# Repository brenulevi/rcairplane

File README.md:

# RC Airplane

### Used components:
Airplane:
- 1x ESP32 DevKit 1
- 1x nRF24L01+ PA/LNA Ext. Antenna
- 1x ESC 30A
- 1x Brushless DC Motor 2200kv
- 4x 9g Servo Motor
- 4x LED (1R, 1G, 2W)
- 4x Resistor 330
- 1x Polarized Capacitor 10uF
- 1x AMS1117-3.3V
- 1x UBEC 5V/3A Freewing
- 1x MPU6050
- 1x BMP280
- 1x ADS1115
- 1x 5200mAh 3S Lipo Battery

Control:
- 1x Arduino Nano
- 1x nRF24L01+ PA/LNA Ext. Antenna

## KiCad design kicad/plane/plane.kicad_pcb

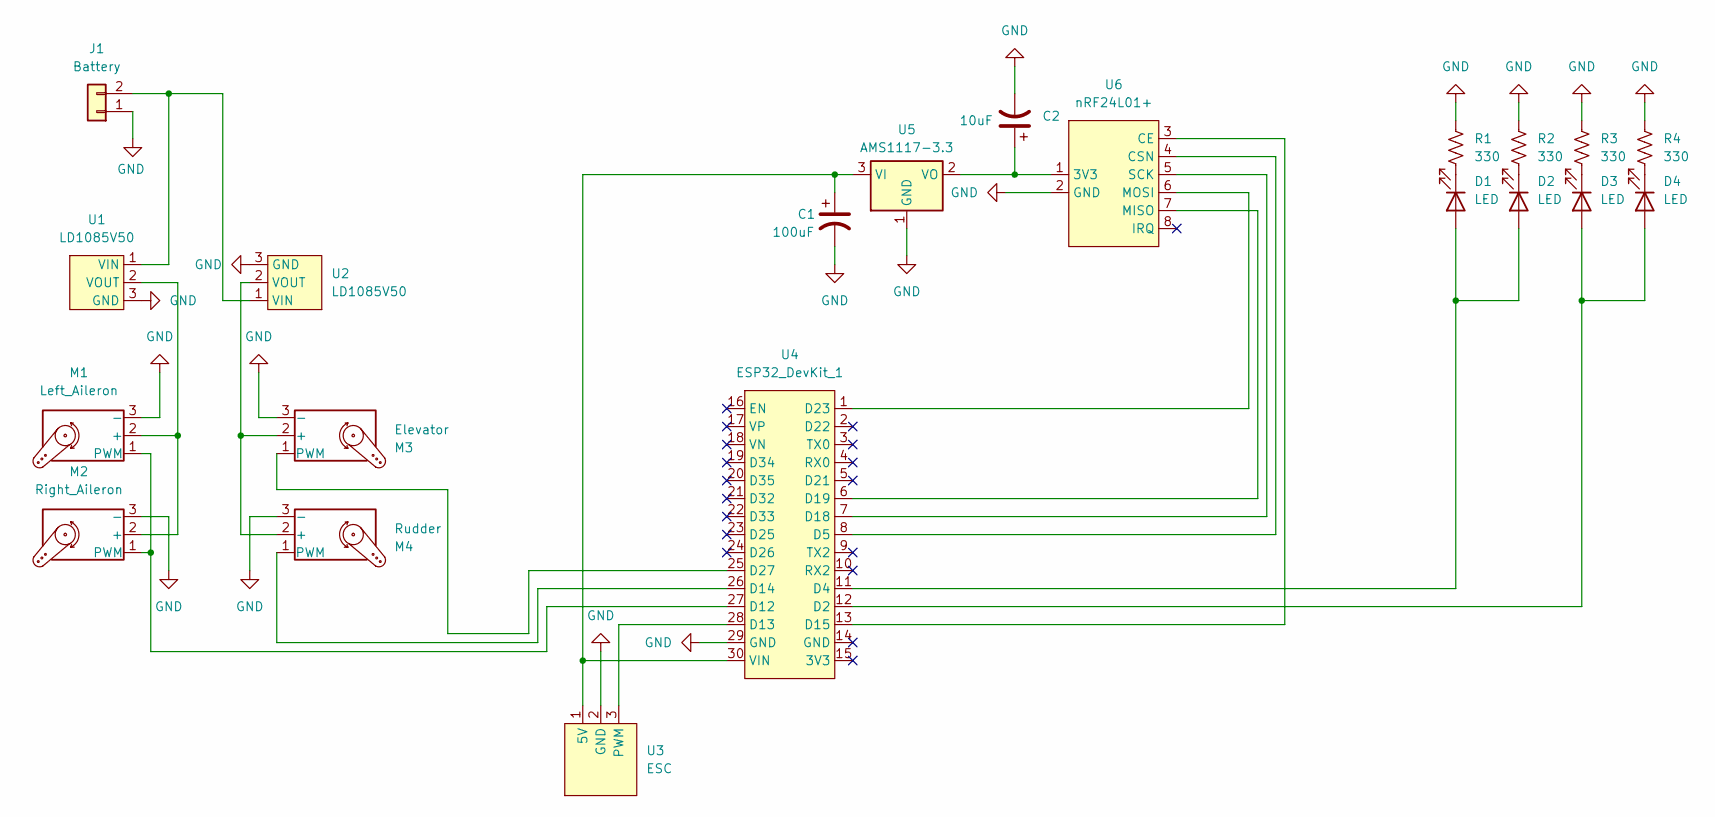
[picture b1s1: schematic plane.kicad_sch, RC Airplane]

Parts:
C1: 100uF; CP_Radial_D8.0mm_P2.50mm
C2: 10uF; CP_Radial_D8.0mm_P2.50mm
D1, D2, D3, D4: LED; PinHeader_1x02_P2.54mm_Vertical
J1: Battery; 14AWG_Wire
M1: Left_Aileron; PinHeader_1x03_P2.54mm_Vertical
M2: Right_Aileron; PinHeader_1x03_P2.54mm_Vertical
M3: Elevator; PinHeader_1x03_P2.54mm_Vertical
M4: Rudder; PinHeader_1x03_P2.54mm_Vertical
R1, R2, R3, R4: 330; R_Axial_DIN0207_L6.3mm_D2.5mm_P10.16mm_Horizontal
U1, U2: LD1085V50
U3: ESC; PinHeader_1x03_P2.54mm_Vertical
U4: ESP32_DevKit_1; ESP32_DevKit_C
U5: AMS1117-3.3; SOT-223-3_TabPin2
U6: nRF24L01+

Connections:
GND: C1.2, C2.2, J1.1, M1.3 (-), M2.3 (-), M3.3 (-), M4.3 (-), R1.1, R2.1, R3.1, R4.1, U1.3 (GND), U2.3 (GND), U3.2 (GND), U4.29 (GND), U5.1 (GND), U6.2 (GND)
unnamed: D1.2 (A), D2.2 (A), U4.11 (D4)
unnamed: D1.1 (K), R1.2
unnamed: D2.1 (K), R2.2
unnamed: D3.2 (A), D4.2 (A), U4.12 (D2)
unnamed: D3.1 (K), R3.2
unnamed: D4.1 (K), R4.2
unnamed: J1.2, U1.1 (VIN), U2.1 (VIN)
unnamed: M1.2 (+), M2.2 (+), U1.2 (VOUT)
unnamed: M1.1 (PWM), M2.1 (PWM), U4.27 (D12)
unnamed: M3.2 (+), M4.2 (+), U2.2 (VOUT)
unnamed: M3.1 (PWM), U4.25 (D27)
unnamed: M4.1 (PWM), U4.26 (D14)
unnamed: C1.1, U3.1 (5V), U4.30 (VIN), U5.3 (VI)
unnamed: U3.3 (PWM), U4.28 (D13)
unnamed: U4.8 (D5), U6.4 (CSN)
unnamed: U4.13 (D15), U6.3 (CE)
unnamed: U4.7 (D18), U6.5 (SCK)
unnamed: U4.6 (D19), U6.7 (MISO)
unnamed: U4.1 (D23), U6.6 (MOSI)
unnamed: C2.1, U5.2 (VO), U6.1 (3V3)

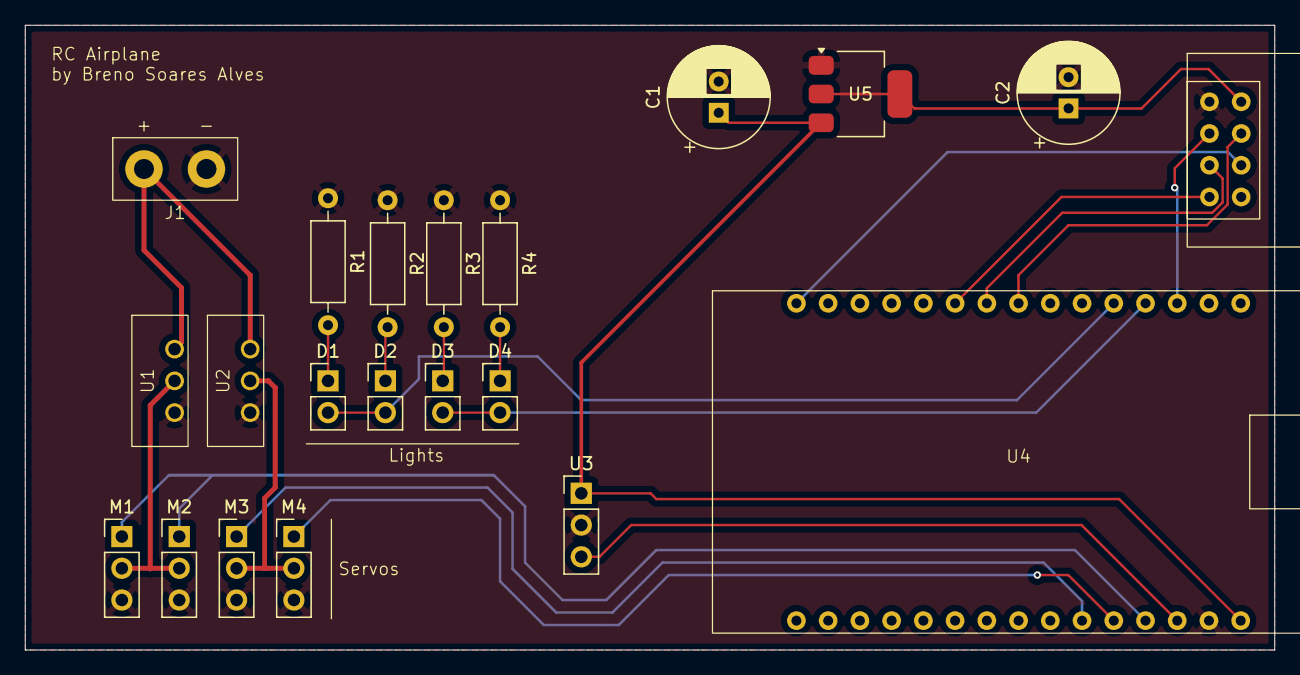
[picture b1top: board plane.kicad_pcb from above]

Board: 2 copper layers, 100.0 x 50.0 mm, 21 parts (0 on the bottom side), 21 nets.

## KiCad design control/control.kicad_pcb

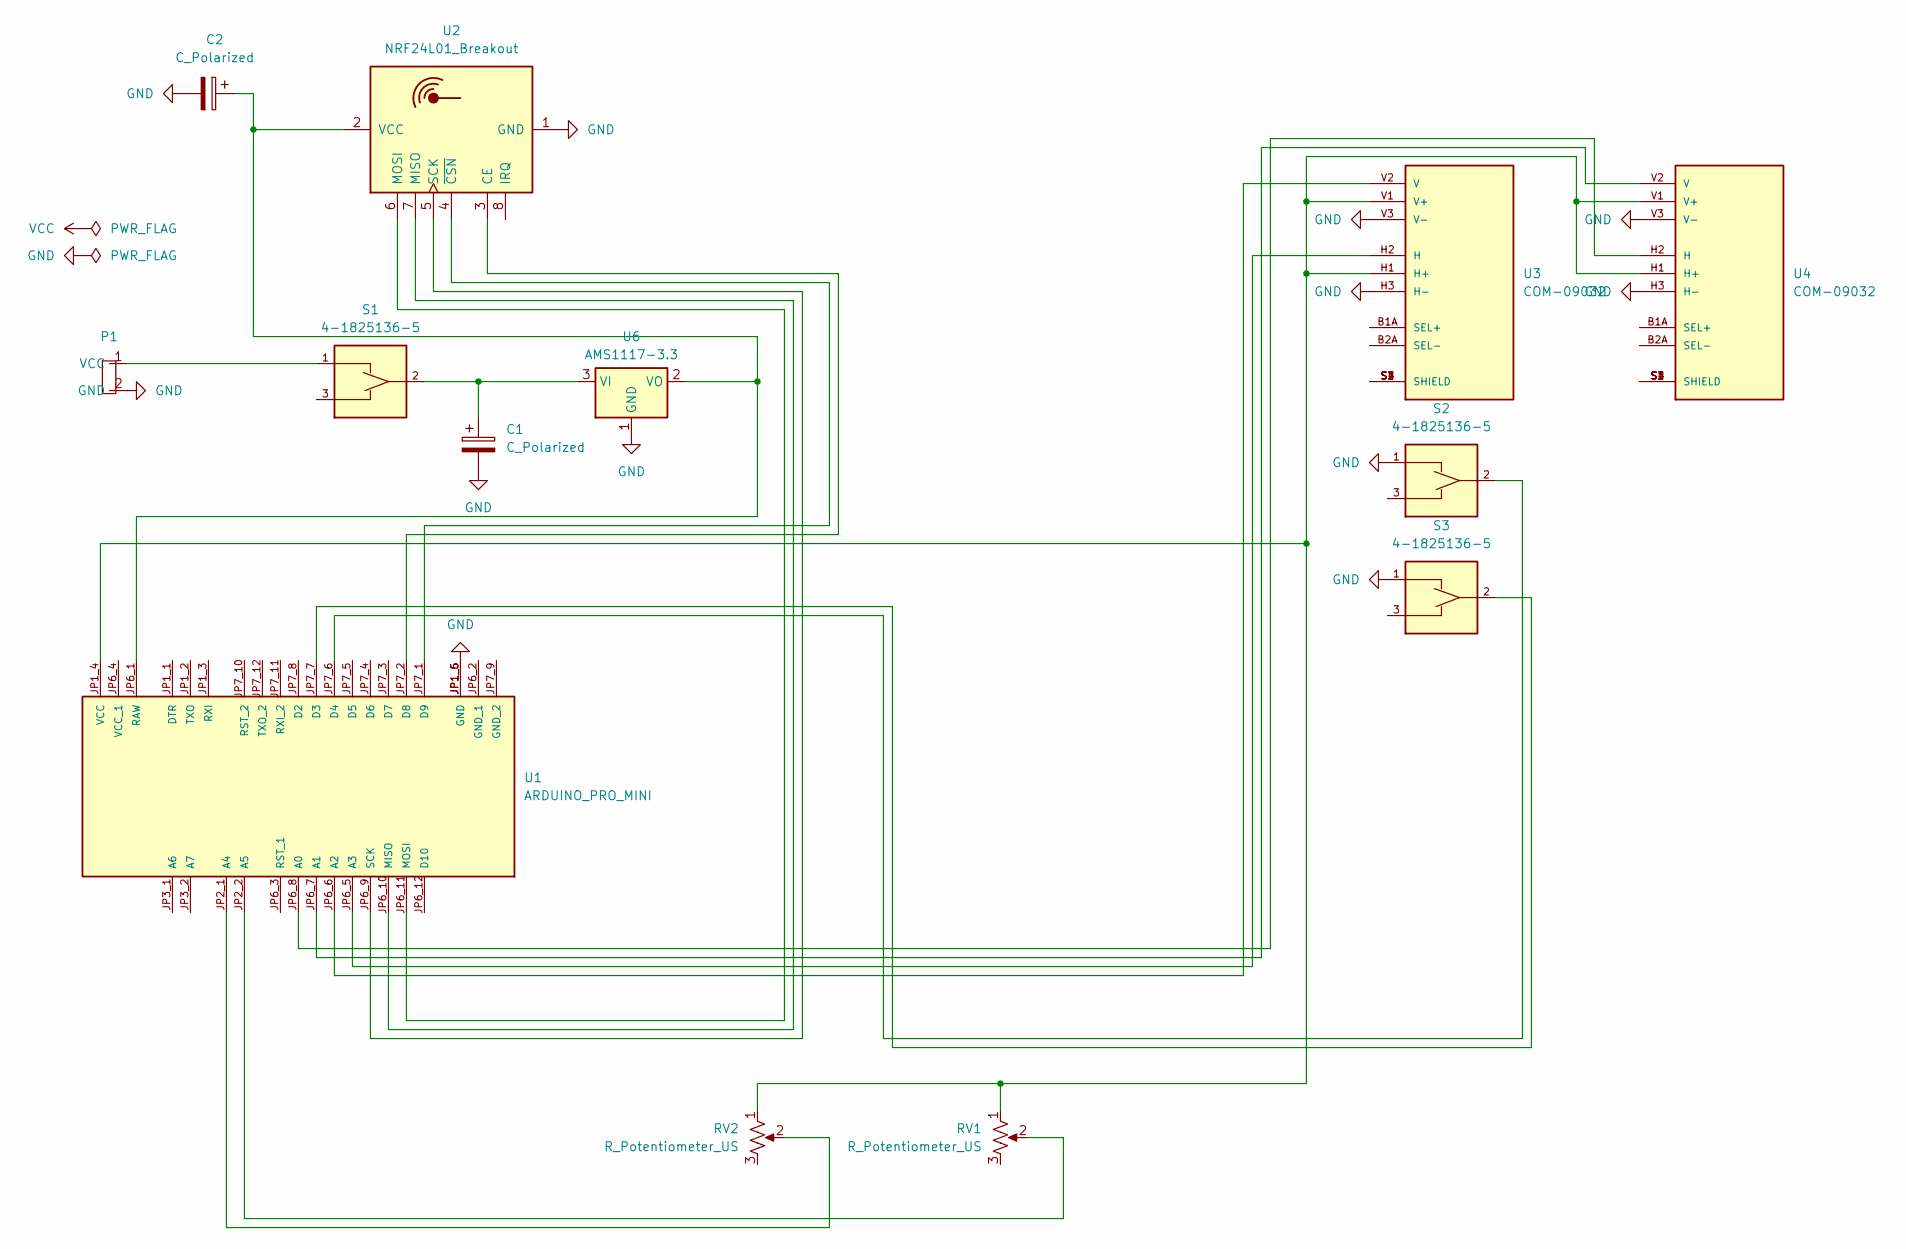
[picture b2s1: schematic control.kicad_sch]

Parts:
C1, C2: C_Polarized; CP_Radial_D4.0mm_P1.50mm
P1: POWER
RV1, RV2: R_Potentiometer_US; Potentiometer_Piher_PC-16_Single_Vertical
S1, S2, S3: 4-1825136-5; TE_4-1825136-5; PART_REV A7
U1: ARDUINO_PRO_MINI; MODULE_ARDUINO_PRO_MINI; PARTREV N/A
U2: NRF24L01_Breakout; nRF24L01_Breakout
U3, U4: COM-09032; XDCR_COM-09032; PARTREV N/A
U6: AMS1117-3.3; SOT-223-3_TabPin2

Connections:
GND: C1.2, C2.2, P1.2 (GND), S2.1, S3.1, U1.JP1_5 (GND), U1.JP1_6 (GND), U2.1 (GND), U3.H3 (H-), U3.V3 (V-), U4.H3 (H-), U4.V3 (V-), U6.1 (GND)
unnamed: P1.1 (VCC), S1.1
unnamed: U1.JP6_8 (A0), U4.H2 (H)
unnamed: U1.JP6_7 (A1), U4.V2 (V)
unnamed: U1.JP6_6 (A2), U3.V2 (V)
unnamed: U1.JP6_5 (A3), U3.H2 (H)
unnamed: RV2.2, U1.JP2_1 (A4)
unnamed: RV1.2, U1.JP2_2 (A5)
unnamed: S3.2, U1.JP7_7 (D3)
unnamed: S2.2, U1.JP7_6 (D4)
unnamed: U1.JP7_2 (D8), U2.3 (CE)
unnamed: U1.JP7_1 (D9), U2.4 (~CSN)
unnamed: U1.JP6_10 (MISO), U2.7 (MISO)
unnamed: U1.JP6_11 (MOSI), U2.6 (MOSI)
unnamed: C2.1, U1.JP6_1 (RAW), U2.2 (VCC), U6.2 (VO)
unnamed: U1.JP6_9 (SCK), U2.5 (SCK)
unnamed: RV1.1, RV2.1, U1.JP1_4 (VCC), U3.H1 (H+), U3.V1 (V+), U4.H1 (H+), U4.V1 (V+)
unnamed: U3.S1 (SHIELD), U3.S2 (SHIELD), U3.S3 (SHIELD), U3.S4 (SHIELD)
unnamed: U4.S1 (SHIELD), U4.S2 (SHIELD), U4.S3 (SHIELD), U4.S4 (SHIELD)
unnamed: C1.1, S1.2, U6.3 (VI)

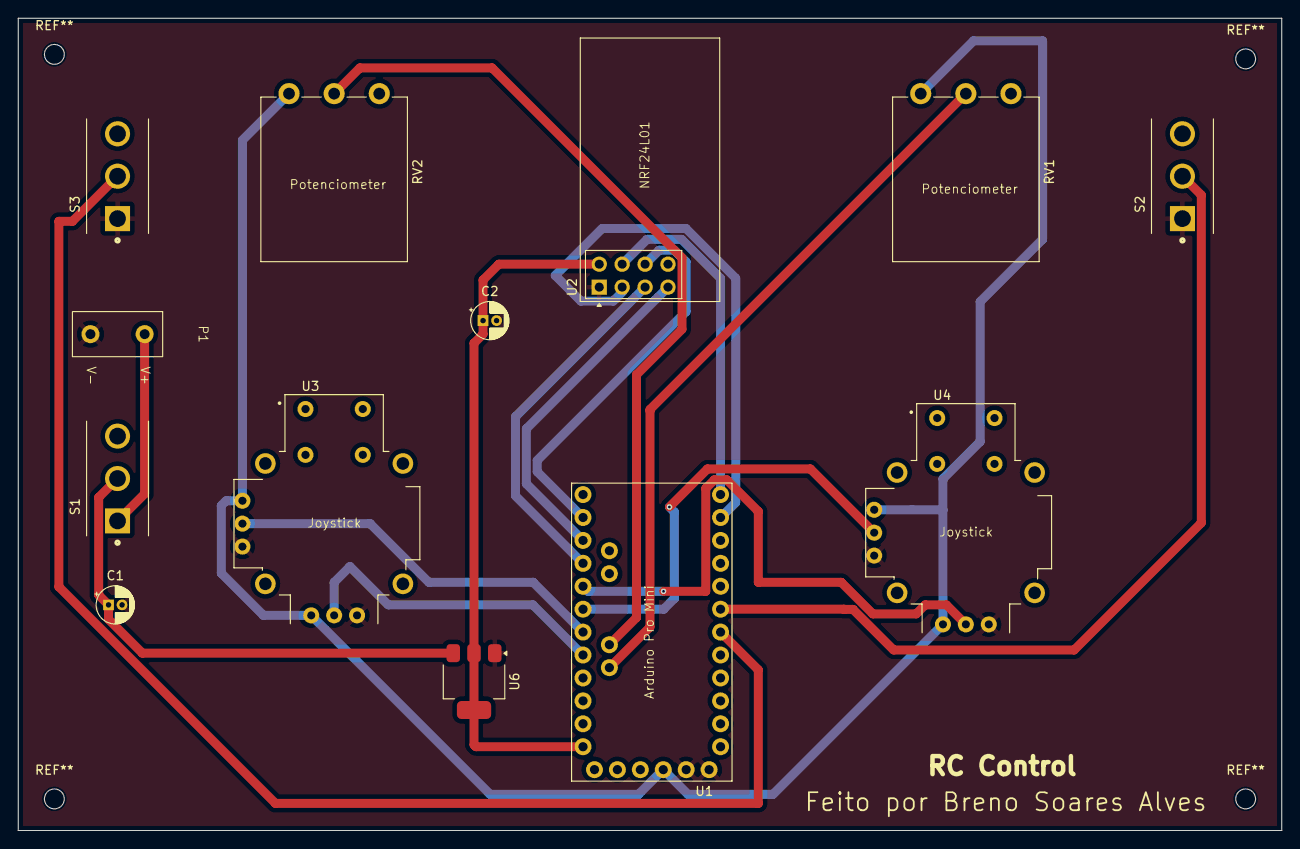
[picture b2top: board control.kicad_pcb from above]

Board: 2 copper layers, 140.0 x 90.0 mm, 13 parts (0 on the bottom side), 20 nets.

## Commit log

2024-09-23 kicad project
2025-03-19 added flight controls module
2025-03-19 added a more... lib style
2025-03-20 added radio module (empty yet), flight controls working
2025-03-21 added rc_radio (im having trouble with nrf24l01 i hate IT)
2025-04-12 added readme
2025-04-12 added radio code
2025-04-17 added plane and control folders
2025-04-17 gpio class abstraction
2025-04-17 added first gpios functions (digital and pwm)
2025-04-19 added i2c interface and ads1115 first module letsgooo (need to test it)
2025-04-19 added servo module and a initial design of airplane (finally) architecture
2025-04-19 added lighting module
2025-04-24 kicad project for plane pcb
2025-04-24 i forgot leds in kicad schematic... ops
2025-04-25 kicad plane project, added first plane code structure
2025-04-25 engine logic (i hope this will prevent a plane brake ksjdjksdjkaj
2025-04-25 simple lighting implemented with strobe and nav, remove throws inside flight controls because attach method sucks
2025-04-27 plane schematic finished
2025-04-28 control code
2025-04-29 first footprintsgit add .
2025-04-29 footprints finished (still need make T Deans connector to battery and ESC), pcb started (size IS A REAL PROBLEM)
2025-04-29 pcb components placement
2025-04-30 pcb without sensors (just rc) is ready to production hehehe
2025-05-02 defined 16awg wire for battery connection and first pcb finished
